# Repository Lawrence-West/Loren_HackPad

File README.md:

# Loren_HackPad
Hi LorenHackPad is 3x3 macropad with a rotary encoder, an OLED display and two status LEDs.

I First started by building the schematics

then I proceded by creating the routing for the pcb

after that I realized the case

as you can see I went for a bit of particular one, since I wanted the components to be visible but also the numpad to be as minimalistic as possible and to reduce to the mininum the weight and the use of material.
and after a bit of code that you can find in the firmware folder this should be the final results
my hackpad feature a knob with wich you can regulate the volume and an oled display to show live time, date and weather. the switches are programmable and I personally chose tto assign them tto some shortcuts such as steam or spotify. 

BOA:

-1 Seed xiao rp2040

-9 through-hole 1N4148 Diodes

-1  EC11 Rotary encoder

-1 0.91 inch OLED display

-2 SK6812 MINI-E LEDs

-4 M3x12mm screws

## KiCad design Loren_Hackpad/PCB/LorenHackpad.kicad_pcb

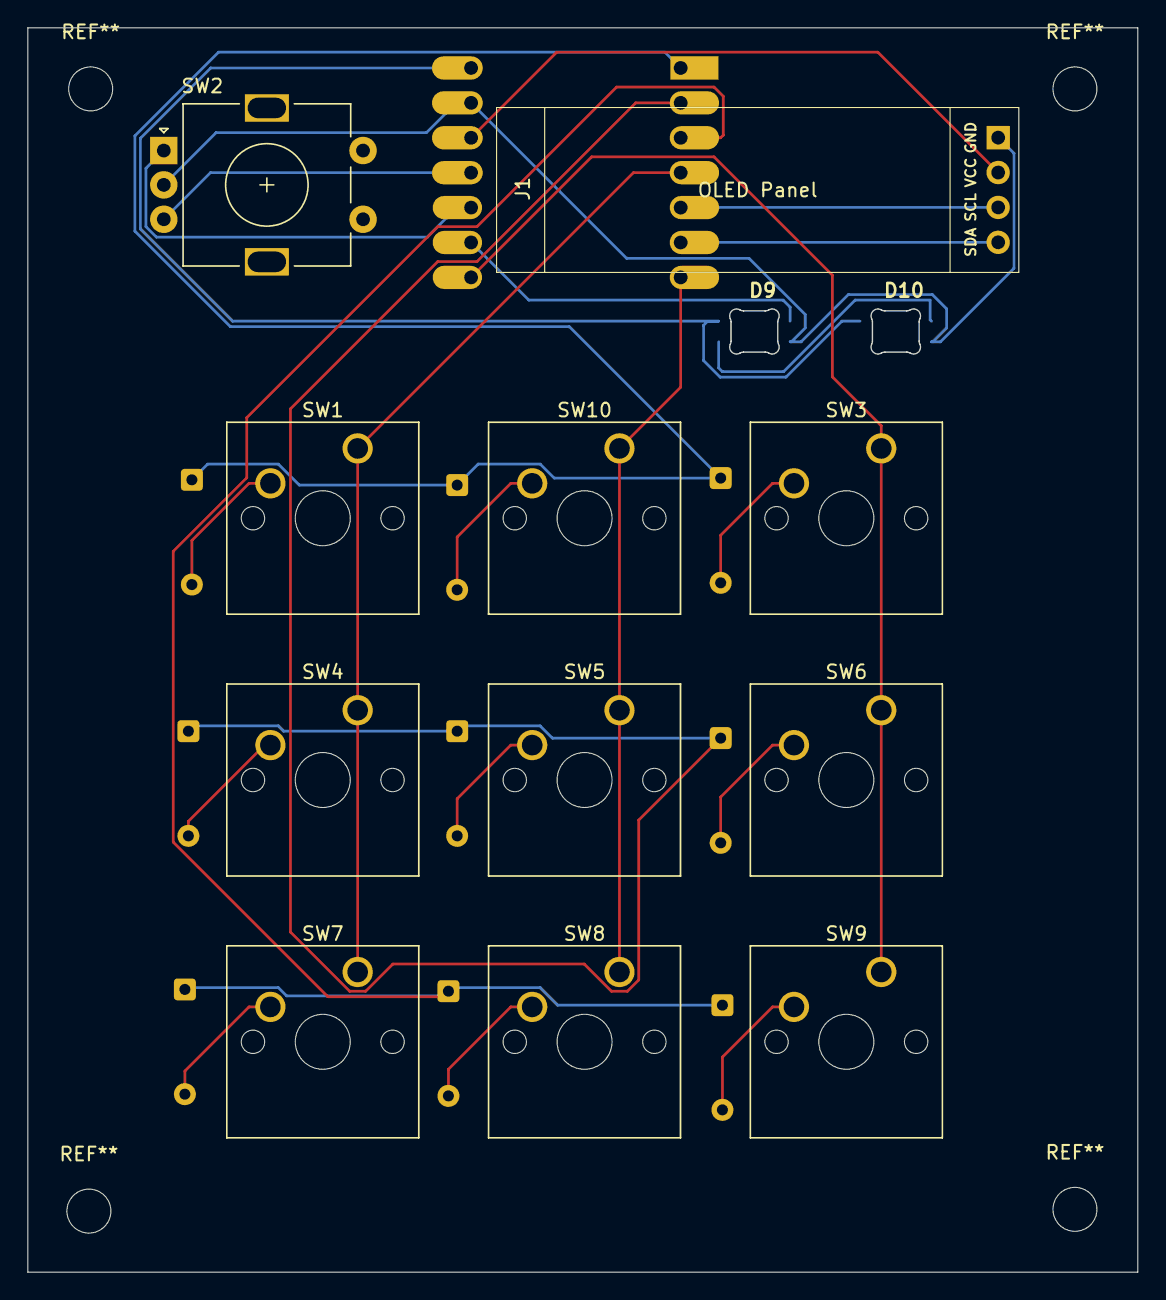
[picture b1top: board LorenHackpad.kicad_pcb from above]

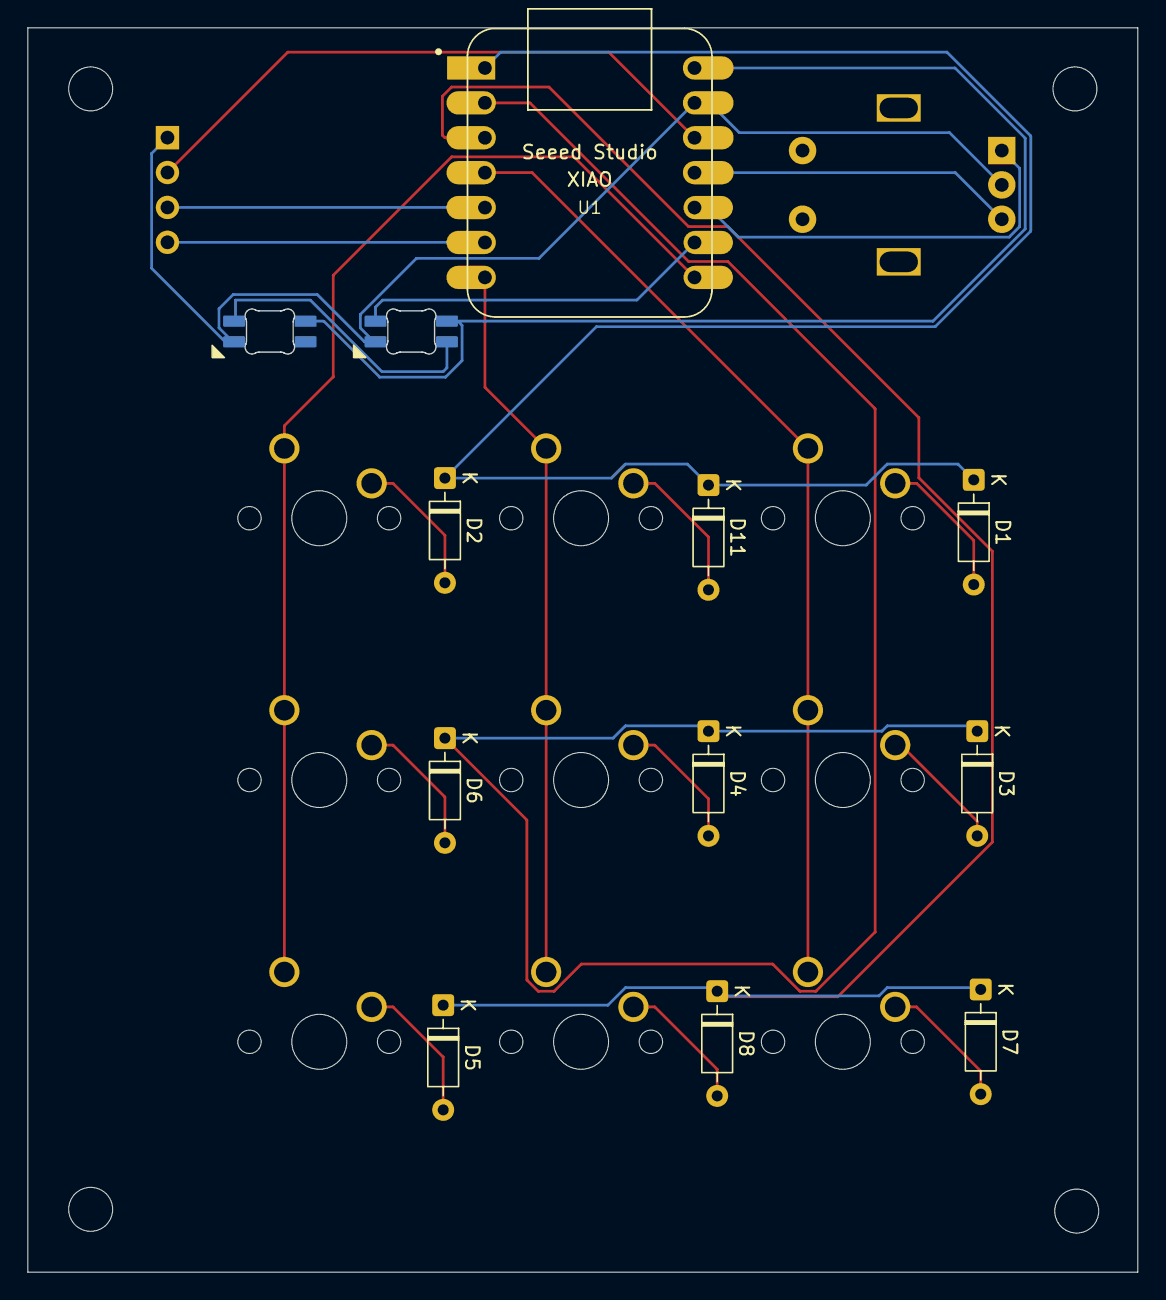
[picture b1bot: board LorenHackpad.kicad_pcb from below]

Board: 2 copper layers, 80.7 x 90.5 mm, 23 parts (10 on the bottom side), 24 nets.

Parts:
D1, D2, D3, D4, D5, D6, D7, D8, D11: 1N4148; D_DO-35_SOD27_P7.62mm_Horizontal
D9, D10: SK6812MINI-E; SK6812MINI-E_fixed
J1: OLED_display; SSD1306-0.91-OLED-4pin-128x32
SW1, SW3, SW4, SW5, SW6, SW7, SW8, SW9, SW10: SW_Push; SW_Cherry_MX_1.00u_PCB
SW2: RotaryEncoder_Switch; RotaryEncoder_Alps_EC11E-Switch_Vertical_H20mm
U1: XIAO-RP2040-DIP; XIAO-Generic-Hybrid-14P-2.54-21X17.8MM

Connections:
+3V3: J1.2, U1.12 (3V3)
+5V: D9.1 (VDD), D10.1 (VDD), U1.14 (VBUS)
COL0: SW1.1, SW4.1, SW7.1, U1.4 (GPIO29/ADC3/A3)
COL1: SW5.1, SW8.1, SW10.1, U1.7 (GPIO0/TX)
COL2: SW3.1, SW6.1, SW9.1, U1.8 (GPIO1/RX)
EC11A: SW2.A, U1.10 (GPIO4/MISO)
EC11B: SW2.B, U1.11 (GPIO3/MOSI)
GND: D9.3 (VSS), D10.3 (VSS), J1.1, SW2.C, U1.13 (GND)
unnamed: D1.2 (A), SW1.2
unnamed: D2.2 (A), SW3.2
unnamed: D3.2 (A), SW4.2
unnamed: D4.2 (A), SW5.2
unnamed: D5.2 (A), SW9.2
unnamed: D6.2 (A), SW6.2
unnamed: D7.2 (A), SW7.2
unnamed: D8.2 (A), SW8.2
unnamed: D9.2 (DOUT), D10.4 (DIN)
unnamed: D11.2 (A), SW10.2
ROW0: D1.1 (K), D2.1 (K), D11.1 (K), U1.1 (GPIO26/ADC0/A0)
ROW1: D3.1 (K), D4.1 (K), D6.1 (K), U1.2 (GPIO27/ADC1/A1)
ROW2: D5.1 (K), D7.1 (K), D8.1 (K), U1.3 (GPIO28/ADC2/A2)
SCL: J1.4, U1.6 (GPIO7/SCL)
SDA: J1.3, U1.5 (GPIO6/SDA)
SK6812MINI-E: D9.4 (DIN), U1.9 (GPIO2/SCK)
